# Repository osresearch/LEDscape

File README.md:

DANGER!
=======

This code works with the PRU units on the Beagle Bone and can easily
cause *hard crashes*.  It is still being debugged and developed.
Be careful hot-plugging things into the headers -- it is possible to
damage the pin drivers and cause problems in the ARM, especially if
there are +5V signals involved.

Overview
========

The WS281x LED chips are built like shift registers and make for very
easy LED strip construction.  The signals are duty-cycle modulated,
with a 0 measuring 250 ns long and a 1 being 600 ns long, and 1250 ns
between bits.  Since this doesn't map to normal SPI hardware and requires
an 800 KHz bit clock, it is typically handled with a dedicated microcontroller
or DMA hardware on something like the Teensy 3.

However, the TI AM335x ARM Cortex-A8 in the BeagleBone Black has two
programmable "microcontrollers" built into the CPU that can handle realtime
tasks and also access the ARM's memory.  This allows things that
might have been delegated to external devices to be handled without
any additional hardware, and without the overhead of clocking data out
the USB port.

The frames are stored in memory as a series of 4-byte pixels in the
order GRBA, packed in strip-major order.  This means that it looks
like this in RAM:

	S0P0 S1P0 S2P0 ... S31P0 S0P1 S1P1 ... S31P1 S0P2 S1P2 ... S31P2

This way length of the strip can be variable, although the memory used
will depend on the length of the longest strip.  4 * 32 * longest strip
bytes are required per frame buffer.  The maximum frame rate also depends
on the length of th elongest strip.

API
===

<ledscape.h> defines the API.  The sample rgb-test program pulses
the first three LEDs in red, green and blue.  The key components are:

	ledscape_t * ledscape_init(unsigned num_pixels)
	ledscape_frame_t * ledscape_frame(ledscape_t*, unsigned frame_num);
	ledscape_draw(ledscape_t*, unsigned frame_num);
	unsigned ledscape_wait(ledscape_t*)

You can double buffer like this:

	const int num_pixels = 256;
	ledscape_t * const leds = ledscape_init(num_pixels);

	unsigned i = 0;
	while (1)
	{
		// Alternate frame buffers on each draw command
		const unsigned frame_num = i++ % 2;
		ledscape_frame_t * const frame
			= ledscape_frame(leds, frame_num);

		render(frame);

		// wait for the previous frame to finish;
		ledscape_wait(leds);
		ledscape_draw(leds, frame_num);
	}

	ledscape_close(leds);

The 24-bit RGB data to be displayed is laid out with BRGA format,
since that is how it will be translated during the clock out from the PRU.
The frame buffer is stored as a "strip-major" array of pixels.

	typedef struct {
		uint8_t b;
		uint8_t r;
		uint8_t g;
		uint8_t a;
	} __attribute__((__packed__)) ledscape_pixel_t;

	typedef struct {
		ledscape_pixel_t strip[32];
	} __attribute__((__packed__)) ledscape_frame_t;

Low level API
=============

If you want to poke at the PRU directly, there is a command structure
shared in PRU DRAM that holds a pointer to the current frame buffer,
the length in pixels, a command byte and a response byte.
Once the PRU has cleared the command byte you are free to re-write the
dma address or number of pixels.

	typedef struct
	{
		// in the DDR shared with the PRU
		const uintptr_t pixels_dma;

		// Length in pixels of the longest LED strip.
		unsigned num_pixels;

		// write 1 to start, 0xFF to abort. will be cleared when started
		volatile unsigned command;

		// will have a non-zero response written when done
		volatile unsigned response;
	} __attribute__((__packed__)) ws281x_command_t;

LED Strips
==========

* http://www.adafruit.com/products/1138
* http://www.adafruit.com/datasheets/WS2811.pdf

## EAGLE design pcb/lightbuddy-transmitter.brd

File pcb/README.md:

Here are three PCB designs, for use with LEDscape:

octoscroller: Control 8 16x32 LED matricies directly from a BBB

LEDscape: Driver board for controlling 32 LED strips over RS485 connections
receiver: Receiver board which has 8x RS485 inputs, for control of up to 8 LED strips

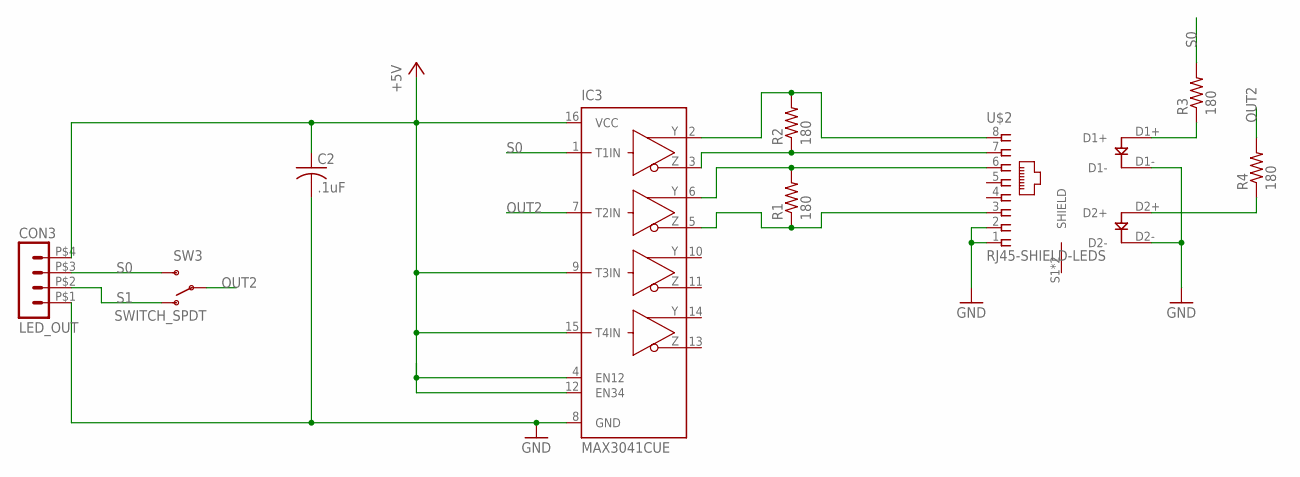
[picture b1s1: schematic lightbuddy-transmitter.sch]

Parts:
C2: .1uF; C0603
CON3: LED_OUT; DUPONT-4P
IC3: MAX3041CUE; TSSOP16
R1, R2, R3, R4: 180; R0603
SW3: SWITCH_SPDT; SWITCH_6P-2POS
U$2: RJ45-SHIELD-LEDS; RJ45-SHIELD-LEDS-ALT

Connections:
+5V: C2.1, CON3.P$4 (4), IC3.4 (EN12), IC3.9 (T3IN), IC3.12 (EN34), IC3.15 (T4IN), IC3.16 (VCC)
GND: C2.2, CON3.P$1 (1), IC3.8 (GND), U$2.1 (8), U$2.2 (7), U$2.D1-, U$2.D2-
unnamed: R3.1, U$2.D1+
unnamed: R4.1, U$2.D2+
unnamed: IC3.5 (Z2), R1.1, U$2.3 (6)
unnamed: IC3.2 (Y1), R2.2, U$2.8 (1)
unnamed: IC3.3 (Z1), R2.1, U$2.7 (2)
unnamed: IC3.6 (Y2), R1.2, U$2.6 (3)
OUT2: IC3.7 (T2IN), R4.2, SW3.P0, SW3.P1
S0: CON3.P$3 (3), IC3.1 (T1IN), R3.2, SW3.S0 (S), SW3.S1 (S)
S1: CON3.P$2 (2), SW3.O0 (O), SW3.O1 (O)

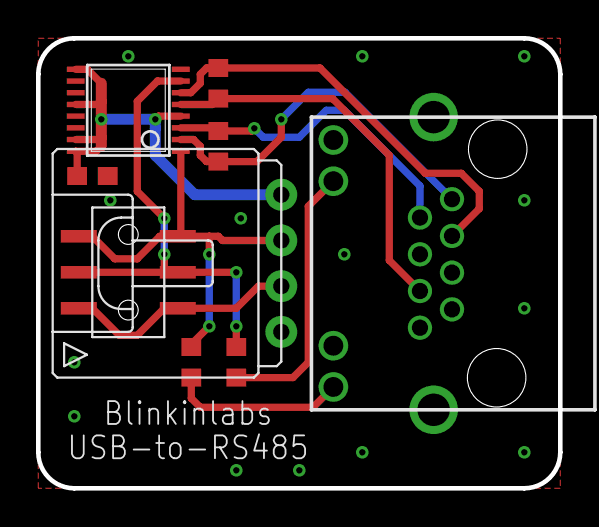
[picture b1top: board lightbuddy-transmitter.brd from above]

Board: 2 copper layers, 29.0 x 25.0 mm, 9 parts (0 on the bottom side), 11 nets.

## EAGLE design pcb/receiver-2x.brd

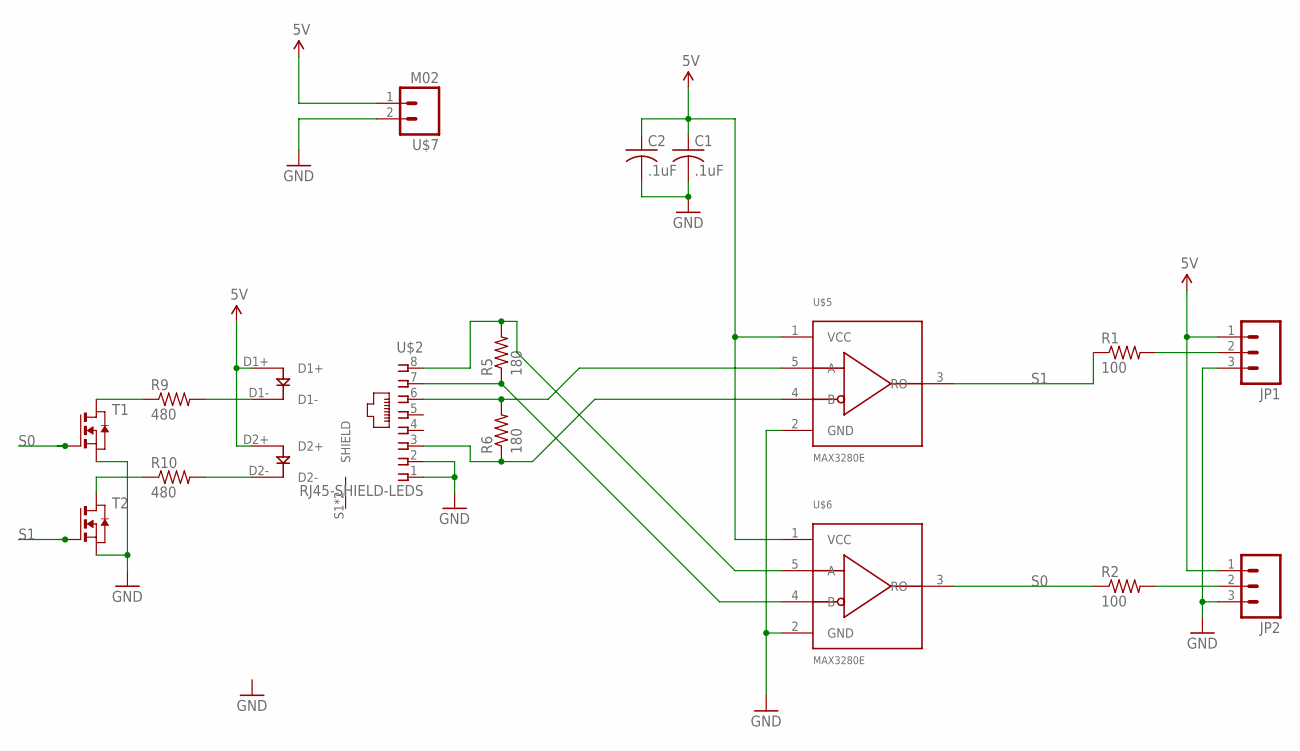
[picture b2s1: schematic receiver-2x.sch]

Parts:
C1, C2: .1uF; C0603
JP1, JP2: M03SCREW-DETACH; SCREWTERMINAL-5MM-3-DETACHABLE
R1, R2: 100; R0603
R5, R6: 180; R0603
R9, R10: 480; R0603
T1, T2: NMOSSOT23; SOT-23
U$2: RJ45-SHIELD-LEDS; RJ45-SHIELD-LEDS-ALT
U$5, U$6: MAX3280E; SOT23-5L
U$7: M02; SCREWTERMINAL-5MM-2-DETACHABLE

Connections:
5V: C1.1, C2.1, JP1.1, JP2.1, U$2.D1+, U$2.D2+, U$5.1 (VCC), U$6.1 (VCC), U$7.1
GND: C1.2, C2.2, JP1.3, JP2.3, T1.2 (S), T2.2 (S), U$2.1 (8), U$2.2 (7), U$5.2 (GND), U$6.2 (GND), U$7.2
unnamed: JP1.2, R1.2
unnamed: JP2.2, R2.2
unnamed: R10.2, U$2.D2-
unnamed: R9.2, U$2.D1-
unnamed: R10.1, T2.1 (D)
unnamed: R9.1, T1.1 (D)
S0: R2.1, T1.3 (G), U$6.3 (RO)
S0_IN+: R5.2, U$2.8 (1), U$6.5 (A)
S0_IN-: R5.1, U$2.7 (2), U$6.4 (B)
S1: R1.1, T2.3 (G), U$5.3 (RO)
S1_IN+: R6.2, U$2.6 (3), U$5.5 (A)
S1_IN-: R6.1, U$2.3 (6), U$5.4 (B)

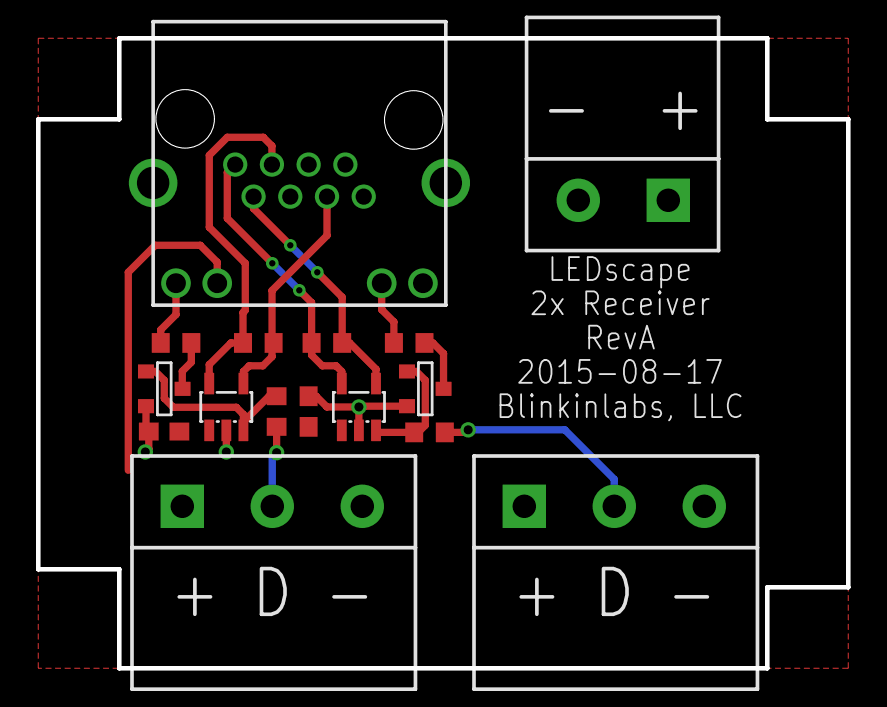
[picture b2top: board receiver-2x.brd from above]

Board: 2 copper layers, 45.0 x 35.0 mm, 17 parts (0 on the bottom side), 14 nets.

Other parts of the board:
U$3: DISORIENT_LOGO

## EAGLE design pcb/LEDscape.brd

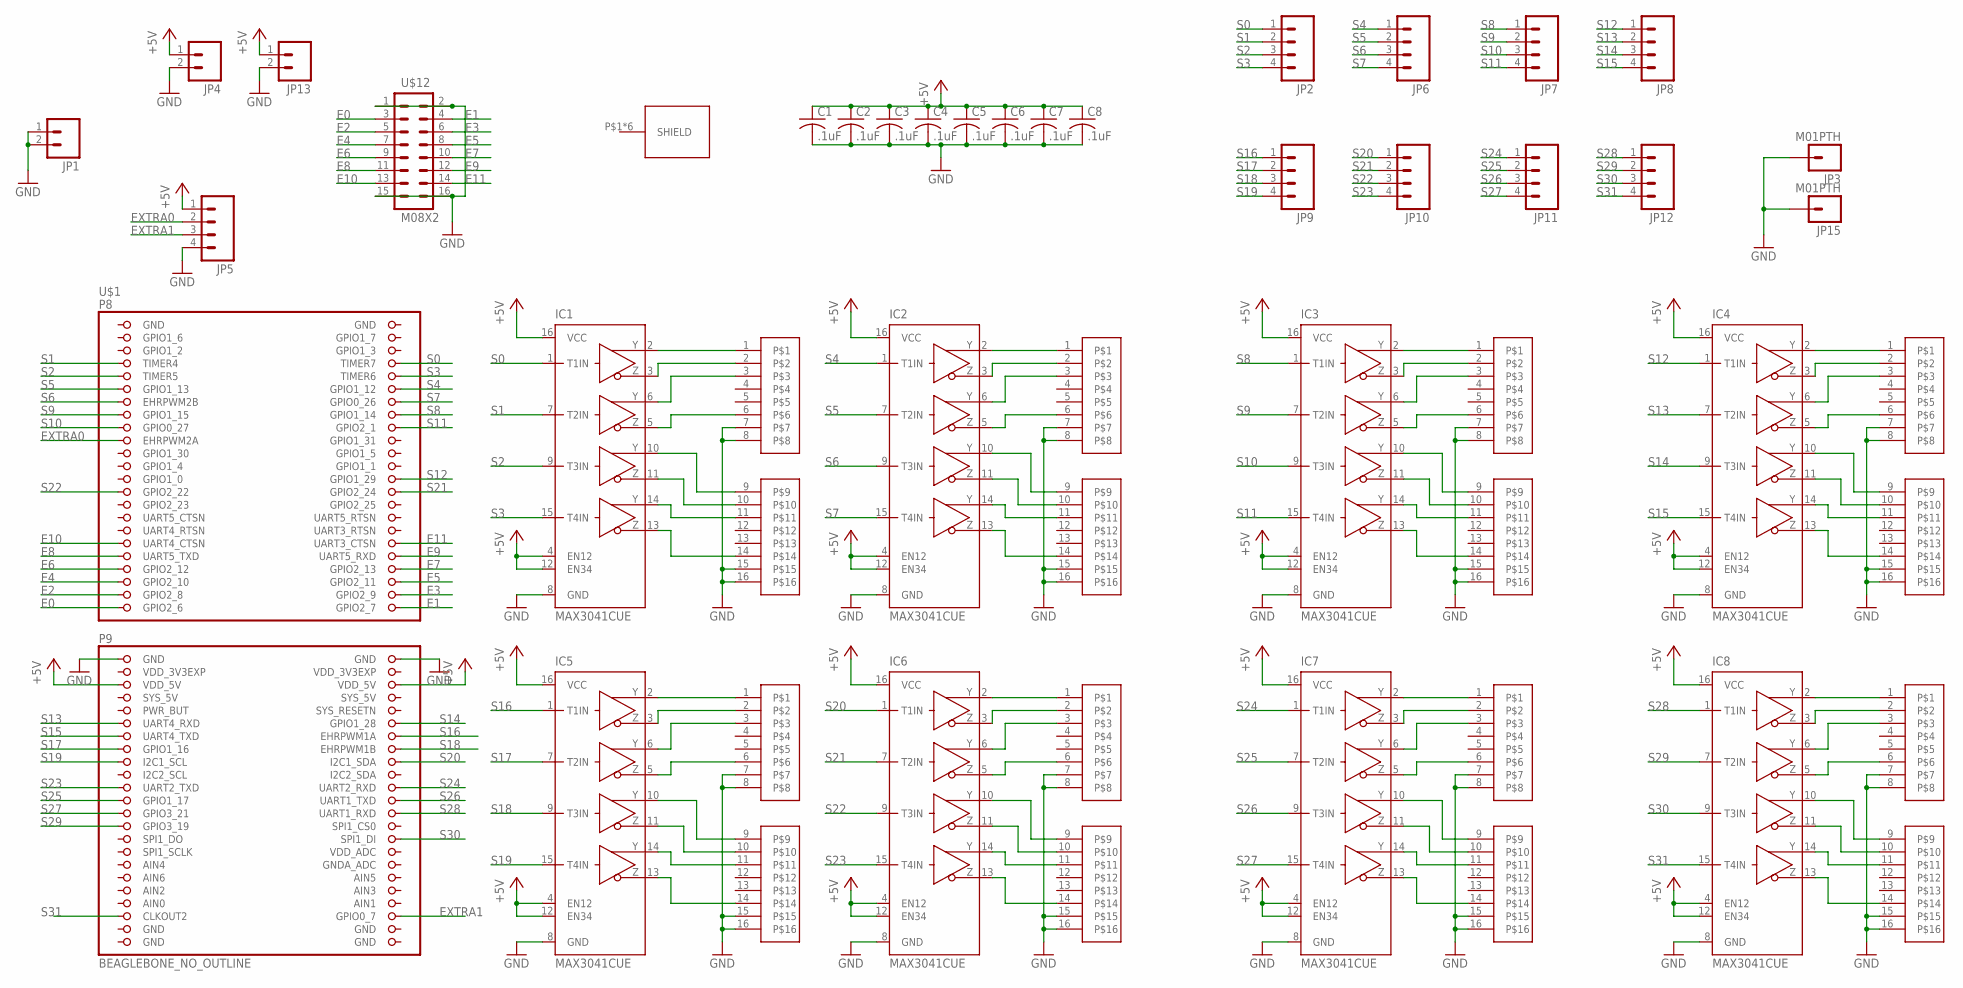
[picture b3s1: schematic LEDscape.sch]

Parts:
C1, C2, C3, C4, C5, C6, C7, C8: .1uF; C0603
IC1, IC2, IC3, IC4, IC5, IC6, IC7, IC8: MAX3041CUE; TSSOP16
JP1, JP4, JP13: M025MM; SCREWTERMINAL-5MM-2
JP2, JP5, JP6, JP7, JP8, JP9, JP10, JP11, JP12: M041X04_NO_SILK; 1X04_NO_SILK
JP3, JP15: M01PTH; 1X01
U$1: BEAGLEBONE_NO_OUTLINE; BEAGLEBONE_SHIELD_NO_OUTLINE
U$2: RJ45_8X2_BASE
U$3, U$4, U$5, U$6, U$7, U$8, U$9, U$10: RJ45_8X2_JACK
U$12: M08X2; 2X8

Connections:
+5V: C1.1, C2.1, C3.1, C4.1, C5.1, C6.1, C7.1, C8.1, IC1.4 (EN12), IC1.12 (EN34), IC1.16 (VCC), IC2.4 (EN12), IC2.12 (EN34), IC2.16 (VCC), IC3.4 (EN12), IC3.12 (EN34), IC3.16 (VCC), IC4.4 (EN12), IC4.12 (EN34), IC4.16 (VCC), IC5.4 (EN12), IC5.12 (EN34), IC5.16 (VCC), IC6.4 (EN12), IC6.12 (EN34), IC6.16 (VCC), IC7.4 (EN12), IC7.12 (EN34), IC7.16 (VCC), IC8.4 (EN12), IC8.12 (EN34), IC8.16 (VCC), JP4.1, JP5.1, JP13.1, U$1.51 (VDD_5V), U$1.52 (VDD_5V)
AIN0: U$1.85 (AIN0)
E0: U$1.45 (GPIO2_6), U$12.3
E1: U$1.46 (GPIO2_7), U$12.4
E2: U$1.43 (GPIO2_8), U$12.5
E3: U$1.44 (GPIO2_9), U$12.6
E4: U$1.41 (GPIO2_10), U$12.7
E5: U$1.42 (GPIO2_11), U$12.8
E6: U$1.39 (GPIO2_12), U$12.9
E7: U$1.40 (GPIO2_13), U$12.10
E8: U$1.37 (UART5_TXD), U$12.11
E9: U$1.38 (UART5_RXD), U$12.12
E10: U$1.35 (UART4_CTSN), U$12.13
E11: U$1.36 (UART3_CTSN), U$12.14
EXTRA0: JP5.2, U$1.19 (EHRPWM2A)
EXTRA1: JP5.3, U$1.88 (GPIO0_7)
GND: C1.2, C2.2, C3.2, C4.2, C5.2, C6.2, C7.2, C8.2, IC1.8 (GND), IC2.8 (GND), IC3.8 (GND), IC4.8 (GND), IC5.8 (GND), IC6.8 (GND), IC7.8 (GND), IC8.8 (GND), JP1.1, JP1.2, JP3.1, JP4.2, JP5.4, JP13.2, JP15.1, U$1.1 (GND), U$1.2 (GND), U$1.47 (GND), U$1.48 (GND), U$1.89 (GND), U$1.90 (GND), U$1.91 (GND), U$1.92 (GND), U$3.7, U$3.8, U$3.15, U$3.16, U$4.7, U$4.8, U$4.15, U$4.16, U$5.7, U$5.8, U$5.15, U$5.16, U$6.7, U$6.8, U$6.15, U$6.16, U$7.7, U$7.8, U$7.15, U$7.16, U$8.7, U$8.8, U$8.15, U$8.16, U$9.7, U$9.8, U$9.15, U$9.16, U$10.7, U$10.8, U$10.15, U$10.16, U$12.1, U$12.2, U$12.15, U$12.16
unnamed: IC1.2 (Y1), U$3.1
unnamed: IC1.3 (Z1), U$3.2
unnamed: IC2.2 (Y1), U$4.1
unnamed: IC1.6 (Y2), U$3.3
unnamed: IC1.5 (Z2), U$3.6
unnamed: IC1.10 (Y3), U$3.9
unnamed: IC1.11 (Z3), U$3.10
unnamed: IC1.14 (Y4), U$3.11
unnamed: IC1.13 (Z4), U$3.14
unnamed: IC2.3 (Z1), U$4.2
unnamed: IC6.5 (Z2), U$7.6
unnamed: IC2.6 (Y2), U$4.3
unnamed: IC2.5 (Z2), U$4.6
unnamed: IC3.5 (Z2), U$5.6
unnamed: IC2.10 (Y3), U$4.9
unnamed: IC2.11 (Z3), U$4.10
unnamed: IC2.14 (Y4), U$4.11
unnamed: IC2.13 (Z4), U$4.14
unnamed: IC3.2 (Y1), U$5.1
unnamed: IC3.3 (Z1), U$5.2
unnamed: IC3.6 (Y2), U$5.3
unnamed: IC3.13 (Z4), U$5.14
unnamed: IC3.10 (Y3), U$5.9
unnamed: IC3.11 (Z3), U$5.10
unnamed: IC3.14 (Y4), U$5.11
unnamed: IC7.6 (Y2), U$8.3
unnamed: IC4.2 (Y1), U$9.1
unnamed: IC4.3 (Z1), U$9.2
unnamed: IC4.6 (Y2), U$9.3
unnamed: IC4.5 (Z2), U$9.6
unnamed: IC4.13 (Z4), U$9.14
unnamed: IC4.11 (Z3), U$9.10
unnamed: IC4.14 (Y4), U$9.11
unnamed: IC4.10 (Y3), U$9.9
unnamed: IC5.2 (Y1), U$6.1
unnamed: IC5.3 (Z1), U$6.2
unnamed: IC5.6 (Y2), U$6.3
unnamed: IC5.5 (Z2), U$6.6
unnamed: IC5.10 (Y3), U$6.9
unnamed: IC5.11 (Z3), U$6.10
unnamed: IC5.14 (Y4), U$6.11
unnamed: IC5.13 (Z4), U$6.14
unnamed: IC6.2 (Y1), U$7.1
unnamed: IC6.3 (Z1), U$7.2
unnamed: IC6.6 (Y2), U$7.3
unnamed: IC7.5 (Z2), U$8.6
unnamed: IC6.10 (Y3), U$7.9
unnamed: IC6.11 (Z3), U$7.10
unnamed: IC6.14 (Y4), U$7.11
unnamed: IC6.13 (Z4), U$7.14
unnamed: IC7.2 (Y1), U$8.1
unnamed: IC7.3 (Z1), U$8.2
unnamed: IC7.10 (Y3), U$8.9
unnamed: IC7.14 (Y4), U$8.11
unnamed: IC7.13 (Z4), U$8.14
unnamed: IC7.11 (Z3), U$8.10
unnamed: IC8.6 (Y2), U$10.3
unnamed: IC8.2 (Y1), U$10.1
unnamed: IC8.3 (Z1), U$10.2
unnamed: IC8.5 (Z2), U$10.6
unnamed: IC8.14 (Y4), U$10.11
unnamed: IC8.10 (Y3), U$10.9
unnamed: IC8.11 (Z3), U$10.10
unnamed: IC8.13 (Z4), U$10.14
S0: IC1.1 (T1IN), JP2.1, U$1.8 (TIMER7)
S1: IC1.7 (T2IN), JP2.2, U$1.7 (TIMER4)
S2: IC1.9 (T3IN), JP2.3, U$1.9 (TIMER5)
S3: IC1.15 (T4IN), JP2.4, U$1.10 (TIMER6)
S4: IC2.1 (T1IN), JP6.1, U$1.12 (GPIO1_12)
S5: IC2.7 (T2IN), JP6.2, U$1.11 (GPIO1_13)
S6: IC2.9 (T3IN), JP6.3, U$1.13 (EHRPWM2B)
S7: IC2.15 (T4IN), JP6.4, U$1.14 (GPIO0_26)
S8: IC3.1 (T1IN), JP7.1, U$1.16 (GPIO1_14)
S9: IC3.7 (T2IN), JP7.2, U$1.15 (GPIO1_15)
S10: IC3.9 (T3IN), JP7.3, U$1.17 (GPIO0_27)
S11: IC3.15 (T4IN), JP7.4, U$1.18 (GPIO2_1)
S12: IC4.1 (T1IN), JP8.1, U$1.26 (GPIO1_29)
S13: IC4.7 (T2IN), JP8.2, U$1.57 (UART4_RXD)
S14: IC4.9 (T3IN), JP8.3, U$1.58 (GPIO1_28)
S15: IC4.15 (T4IN), JP8.4, U$1.59 (UART4_TXD)
S16: IC5.1 (T1IN), JP9.1, U$1.60 (EHRPWM1A)
S17: IC5.7 (T2IN), JP9.2, U$1.61 (GPIO1_16)
S18: IC5.9 (T3IN), JP9.3, U$1.62 (EHRPWM1B)
S19: IC5.15 (T4IN), JP9.4, U$1.63 (I2C1_SCL)
S20: IC6.1 (T1IN), JP10.1, U$1.64 (I2C1_SDA)
S21: IC6.7 (T2IN), JP10.2, U$1.28 (GPIO2_24)
S22: IC6.9 (T3IN), JP10.3, U$1.27 (GPIO2_22)
S23: IC6.15 (T4IN), JP10.4, U$1.67 (UART2_TXD)
S24: IC7.1 (T1IN), JP11.1, U$1.68 (UART2_RXD)
S25: IC7.7 (T2IN), JP11.2, U$1.69 (GPIO1_17)
S26: IC7.9 (T3IN), JP11.3, U$1.70 (UART1_TXD)
S27: IC7.15 (T4IN), JP11.4, U$1.71 (GPIO3_21)
S28: IC8.1 (T1IN), JP12.1, U$1.72 (UART1_RXD)
S29: IC8.7 (T2IN), JP12.2, U$1.73 (GPIO3_19)
S30: IC8.9 (T3IN), JP12.3, U$1.76 (SPI1_DI)
S31: IC8.15 (T4IN), JP12.4, U$1.87 (CLKOUT2)
SYS_5V: U$1.53 (SYS_5V)
VDD_3V3EXP: U$1.49 (VDD_3V3EXP), U$1.50 (VDD_3V3EXP)

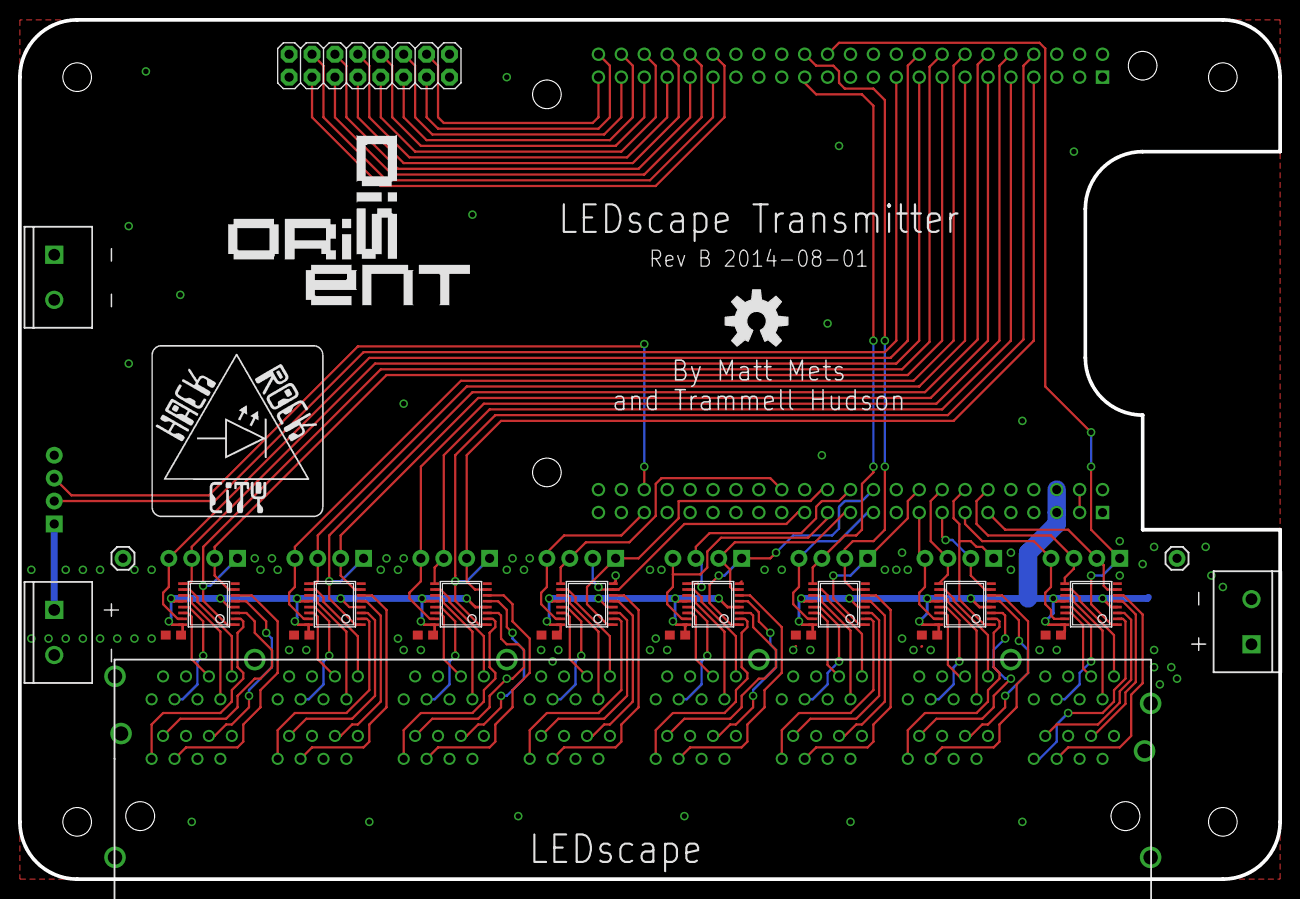
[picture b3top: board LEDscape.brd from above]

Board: 2 copper layers, 139.7 x 95.2 mm, 44 parts (1 on the bottom side), 113 nets.

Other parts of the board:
U$11: OSHW-LOGO-L
U$13: HRC_LOGO_0.75IN
U$14: DISORIENT_LOGO

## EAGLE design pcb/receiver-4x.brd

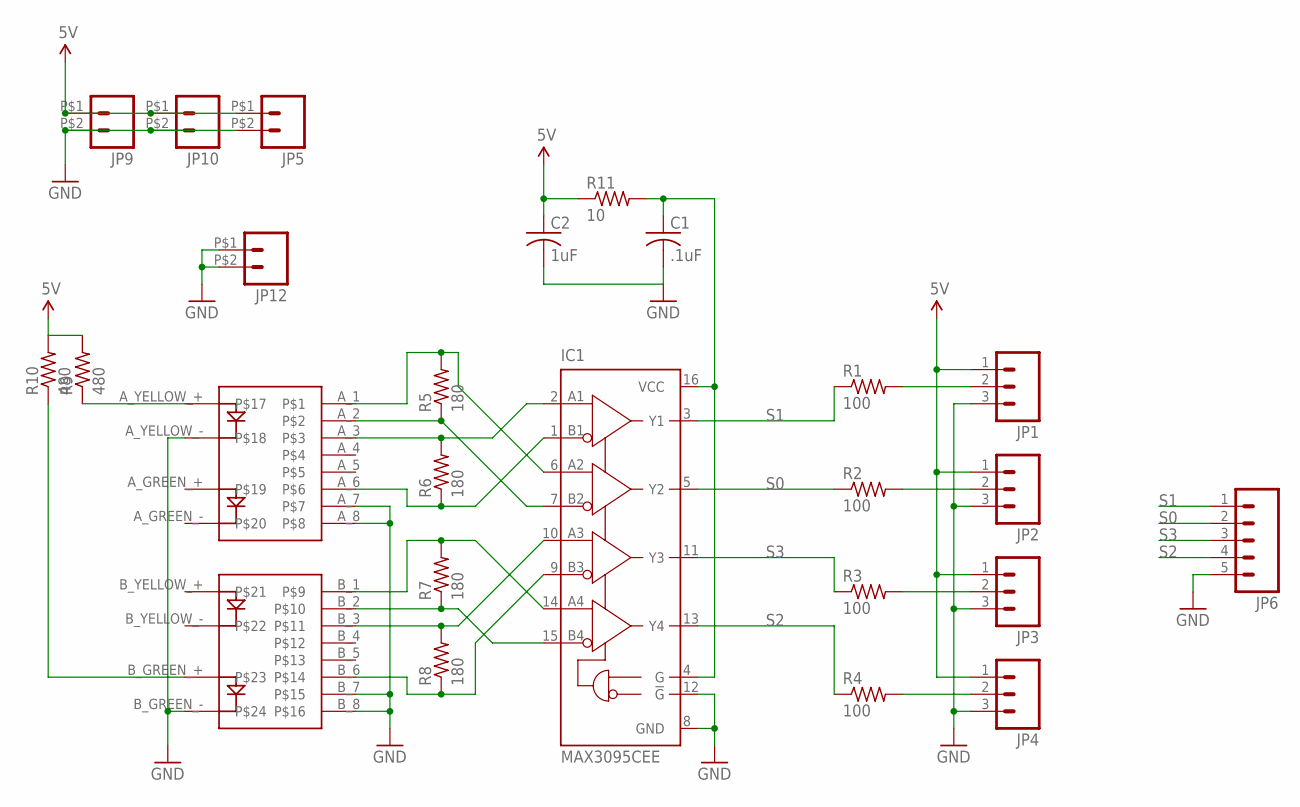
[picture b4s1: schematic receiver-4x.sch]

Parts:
C1: .1uF; C0603
C2: 1uF; C0603
IC1: MAX3095CEE; QSOP16
JP1, JP2, JP3, JP4: M03SCREW-DETACH; SCREWTERMINAL-5MM-3-DETACHABLE
JP5, JP9, JP10, JP12: M026.35MM; SCREWTERMINAL-6.35MM-2
JP6: M05PTH; 1X05
R1, R2, R3, R4: 100; R0603
R5, R6, R7, R8: 180; R0603
R9, R10: 480; R0603
R11: 10; R0603
U$1: RJ45_2X1

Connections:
5V: C2.1, JP1.1, JP2.1, JP3.1, JP4.1, JP5.P$1 (1), JP9.P$1 (1), JP10.P$1 (1), R9.2, R10.2, R11.1
GND: C1.2, C2.2, IC1.8 (GND), IC1.12 (!G), JP1.3, JP2.3, JP3.3, JP4.3, JP5.P$2 (2), JP6.5, JP9.P$2 (2), JP10.P$2 (2), JP12.P$1 (1), JP12.P$2 (2), U$1.A_7, U$1.A_8, U$1.A_YELLOW_-, U$1.B_7, U$1.B_8, U$1.B_GREEN_-
unnamed: JP1.2, R1.2
unnamed: IC1.6 (A2), R5.2, U$1.A_1
unnamed: IC1.7 (B2), R5.1, U$1.A_2
unnamed: JP2.2, R2.2
unnamed: JP3.2, R3.2
unnamed: JP4.2, R4.2
unnamed: IC1.2 (A1), R6.2, U$1.A_3
unnamed: IC1.1 (B1), R6.1, U$1.A_6
unnamed: IC1.14 (A4), R7.2, U$1.B_1
unnamed: IC1.15 (B4), R7.1, U$1.B_2
unnamed: IC1.10 (A3), R8.2, U$1.B_3
unnamed: IC1.9 (B3), R8.1, U$1.B_6
unnamed: R9.1, U$1.A_YELLOW_+
unnamed: R10.1, U$1.B_GREEN_+
unnamed: C1.1, IC1.4 (G), IC1.16 (VCC), R11.2
S0: IC1.5 (Y2), JP6.2, R2.1
S1: IC1.3 (Y1), JP6.1, R1.1
S2: IC1.13 (Y4), JP6.4, R4.1
S3: IC1.11 (Y3), JP6.3, R3.1

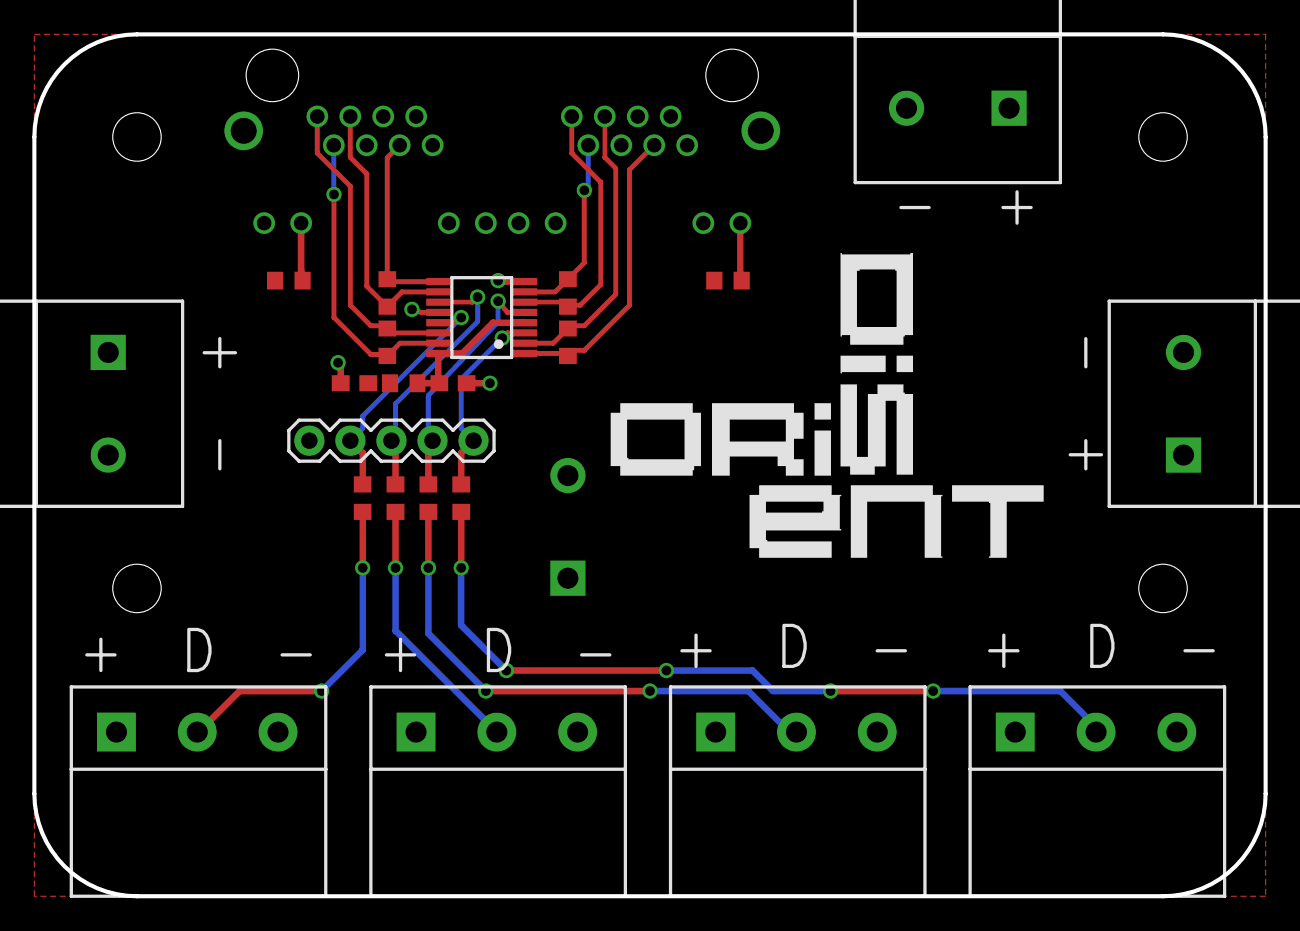
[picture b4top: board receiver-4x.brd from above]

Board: 2 copper layers, 76.2 x 53.3 mm, 25 parts (1 on the bottom side), 21 nets.

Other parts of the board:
U$3: DISORIENT_LOGO

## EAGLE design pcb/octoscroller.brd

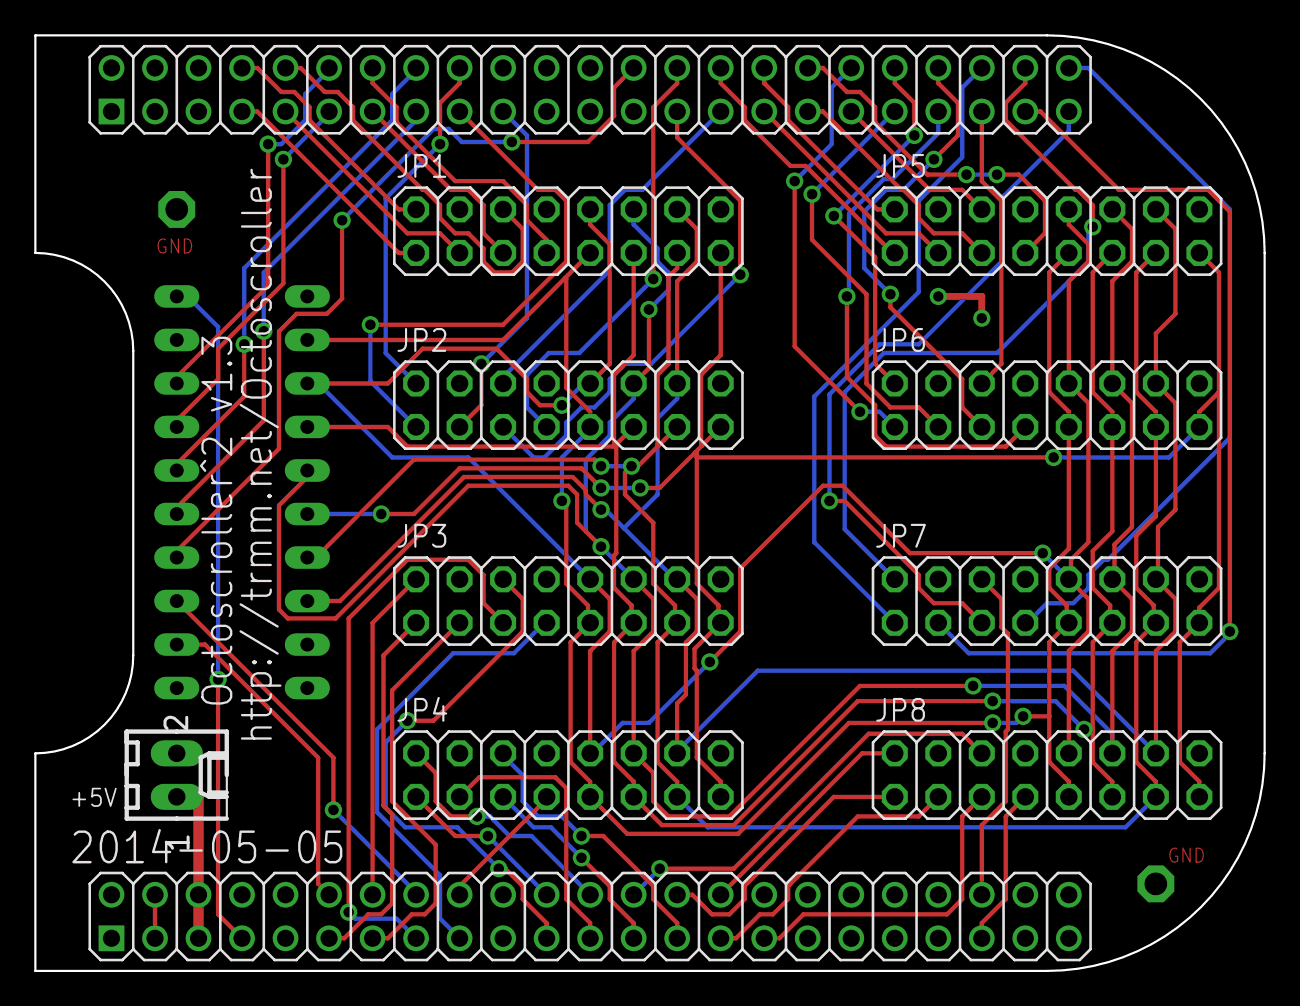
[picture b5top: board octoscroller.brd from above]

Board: 2 copper layers, 71.8 x 54.6 mm, 13 parts (1 on the bottom side), 66 nets.

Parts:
+5V: 22-27-2021-02; 6410-02
IC1: 74LS245N; DIL20
JP1, JP2, JP3, JP4, JP5, JP6, JP7, JP8: 2X08
TP1, TP2: PTR1PAD1-13; P1-13
U$1: BEAGLEBONE_OUTLINE; BEAGLEBONE_SHIELD

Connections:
+5V: IC1.20, U$1.53
+5V-IN: +5V.1, U$1.51, U$1.52
A: IC1.2, JP1.9, JP2.9, JP3.9, JP4.9, JP5.9, JP6.9, JP7.9, JP8.9
A_RAW: IC1.18, U$1.12
B: IC1.3, JP1.10, JP2.10, JP3.10, JP4.10, JP5.10, JP6.10, JP7.10, JP8.10
B1.1: JP1.3, U$1.9
B1.2: JP1.7, U$1.14
B2.1: JP2.3, U$1.19
B2.2: JP2.7, U$1.28
B3.1: JP3.3, U$1.59
B3.2: JP3.7, U$1.63
B4.1: JP4.3, U$1.69
B4.2: JP4.7, U$1.64
B5.1: JP5.3, U$1.31
B5.2: JP5.7, U$1.34
B6.1: JP6.3, U$1.37
B6.2: JP6.7, U$1.39
B7.1: JP7.3, U$1.43
B7.2: JP7.7, U$1.46
B8.1: JP8.3, U$1.75
B8.2: JP8.7, U$1.87
B_RAW: IC1.17, U$1.11
C: IC1.4, JP1.11, JP2.11, JP3.11, JP4.11, JP5.11, JP6.11, JP7.11, JP8.11
CLK: IC1.7, JP1.13, JP2.13, JP3.13, JP4.13, JP5.13, JP6.13, JP7.13, JP8.13
CLK_RAW: IC1.13, U$1.62
C_RAW: IC1.16, U$1.16
D: IC1.5, JP1.12, JP2.12, JP3.12, JP4.12, JP5.12, JP6.12, JP7.12, JP8.12
D_RAW: IC1.15, U$1.15
G1.1: JP1.2, U$1.8
G1.2: JP1.6, U$1.10
G2.1: JP2.2, U$1.18
G2.2: JP2.6, U$1.29
G3.1: JP3.2, U$1.60
G3.2: JP3.6, U$1.67
G4.1: JP4.2, U$1.70
G4.2: JP4.6, U$1.73
G5.1: JP5.2, U$1.32
G5.2: JP5.6, U$1.35
G6.1: JP6.2, U$1.38
G6.2: JP6.6, U$1.41
G7.1: JP7.2, U$1.44
G7.2: JP7.6, U$1.88
G8.1: JP8.2, U$1.76
G8.2: JP8.6, U$1.72
GND: +5V.2, IC1.1, IC1.10, IC1.19, JP1.4, JP1.8, JP1.16, JP2.4, JP2.8, JP2.16, JP3.4, JP3.8, JP3.16, JP4.4, JP4.8, JP4.16, JP5.4, JP5.8, JP5.16, JP6.4, JP6.8, JP6.16, JP7.4, JP7.8, JP7.16, JP8.4, JP8.8, JP8.16, TP1.TP, TP2.TP, U$1.1, U$1.2, U$1.47, U$1.48, U$1.89, U$1.90, U$1.91, U$1.92
LATCH: IC1.8, JP1.14, JP2.14, JP3.14, JP4.14, JP5.14, JP6.14, JP7.14, JP8.14
LATCH_RAW: IC1.12, U$1.58
OE: IC1.6, JP1.15, JP2.15, JP3.15, JP4.15, JP5.15, JP6.15, JP7.15, JP8.15
OE_RAW: IC1.14, U$1.26
R1.1: JP1.1, U$1.7
R1.2: JP1.5, U$1.13
R2.1: JP2.1, U$1.17
R2.2: JP2.5, U$1.27
R3.1: JP3.1, U$1.57
R3.2: JP3.5, U$1.61
R4.1: JP4.1, U$1.68
R4.2: JP4.5, U$1.71
R5.1: JP5.1, U$1.30
R5.2: JP5.5, U$1.33
R6.1: JP6.1, U$1.36
R6.2: JP6.5, U$1.40
R7.1: JP7.1, U$1.42
R7.2: JP7.5, U$1.45
R8.1: JP8.1, U$1.74
R8.2: JP8.5, U$1.77
VDD_3V3EXP: U$1.49, U$1.50

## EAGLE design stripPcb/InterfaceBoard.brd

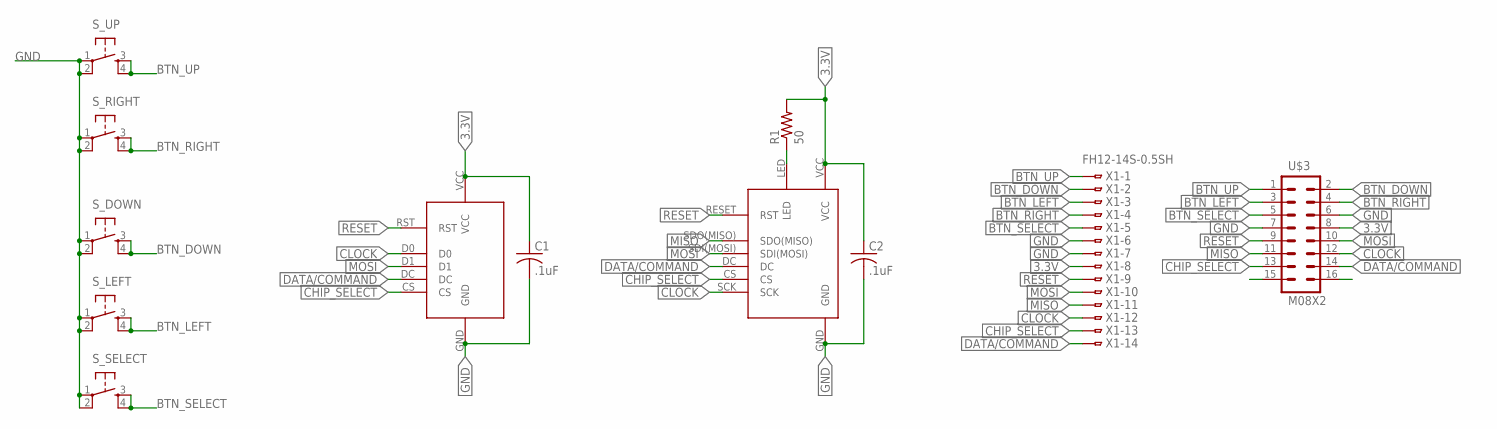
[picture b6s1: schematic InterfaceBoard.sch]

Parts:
C1, C2: .1uF; C0603
R1: 50; R0603
S_DOWN: TAC_SWITCHSMD; TACTILE_SWITCH_SMD
S_LEFT: TAC_SWITCHSMD; TACTILE_SWITCH_SMD
S_RIGHT: TAC_SWITCHSMD; TACTILE_SWITCH_SMD
S_SELECT: TAC_SWITCHSMD; TACTILE_SWITCH_SMD
S_UP: TAC_SWITCHSMD; TACTILE_SWITCH_SMD
U$1: OLED_XYDZ_13
U$2: LCD_QDTECH_22
U$3: M08X2; 2X8
X1: FH12-14S-0.5SH

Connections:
3.3V: C1.1, C2.1, R1.2, U$1.VCC, U$2.VCC, U$3.8, X1.8
BTN_DOWN: S_DOWN.3, S_DOWN.4, U$3.2, X1.2
BTN_LEFT: S_LEFT.3, S_LEFT.4, U$3.3, X1.3
BTN_RIGHT: S_RIGHT.3, S_RIGHT.4, U$3.4, X1.4
BTN_SELECT: S_SELECT.3, S_SELECT.4, U$3.5, X1.5
BTN_UP: S_UP.3, S_UP.4, U$3.1, X1.1
CHIP_SELECT: U$1.CS, U$2.CS, U$3.13, X1.13
CLOCK: U$1.D0, U$2.SCK, U$3.12, X1.12
DATA/COMMAND: U$1.DC, U$2.DC, U$3.14, X1.14
GND: C1.2, C2.2, S_DOWN.1, S_DOWN.2, S_LEFT.1, S_LEFT.2, S_RIGHT.1, S_RIGHT.2, S_SELECT.1, S_SELECT.2, S_UP.1, S_UP.2, U$1.GND, U$2.GND, U$3.6, U$3.7, X1.6, X1.7
MISO: U$2.SDO(MISO), U$3.11, X1.11
MOSI: U$1.D1, U$2.SDI(MOSI), U$3.10, X1.10
unnamed: R1.1, U$2.LED
RESET: U$1.RST, U$2.RESET (RST), U$3.9, X1.9

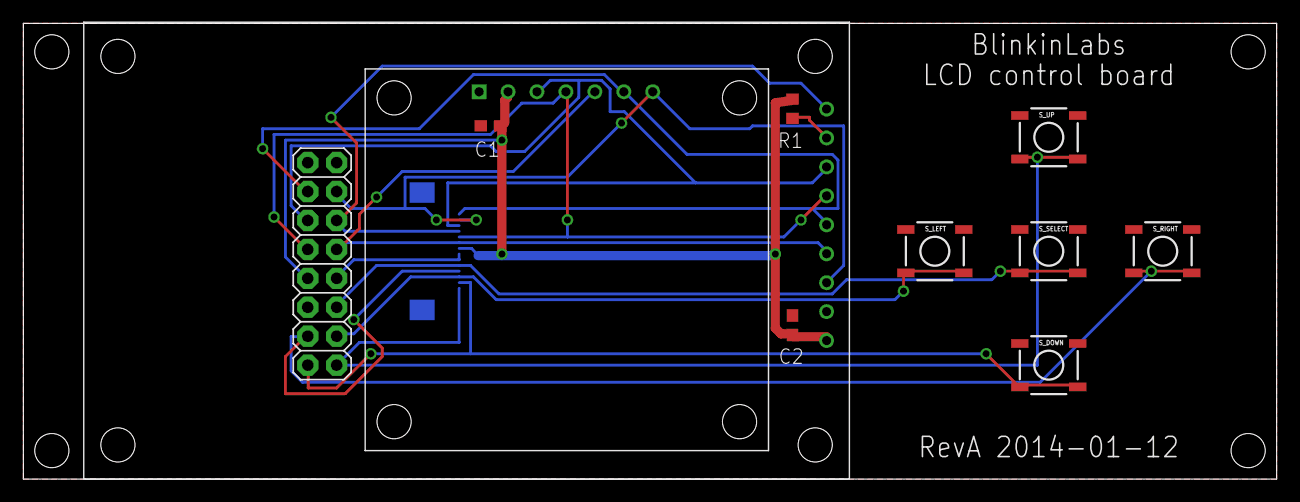
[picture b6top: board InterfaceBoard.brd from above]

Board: 2 copper layers, 110.0 x 40.0 mm, 12 parts (1 on the bottom side), 14 nets.

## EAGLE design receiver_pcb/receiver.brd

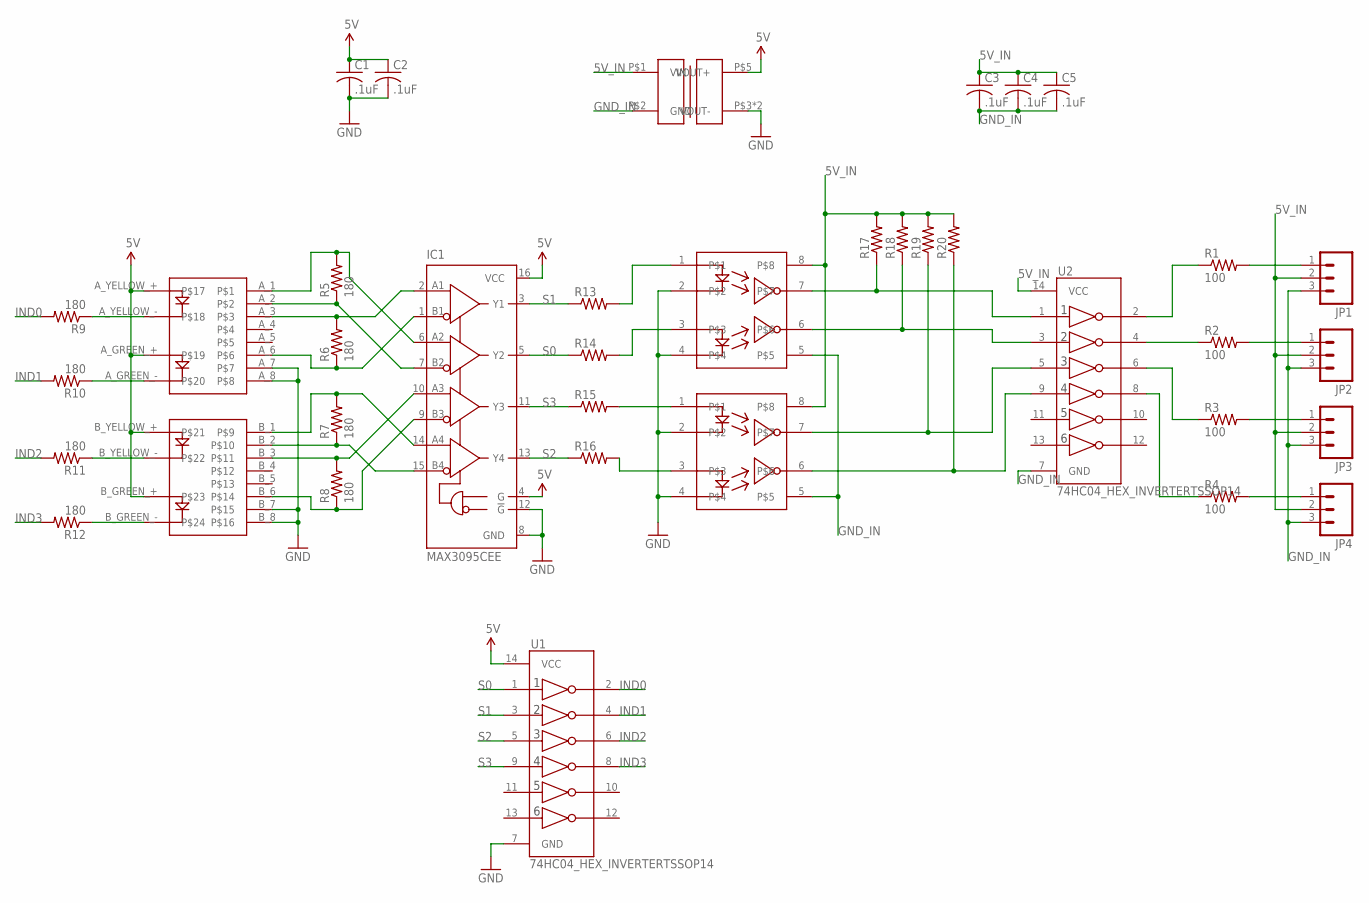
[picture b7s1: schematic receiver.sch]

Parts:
C1, C2, C3, C4, C5: .1uF; C0603
IC1: MAX3095CEE; QSOP16
JP1, JP2, JP3, JP4: M03-SCREW-5MM; SCREWTERMINAL-5MM-3
R1, R2, R3, R4: 100; R0603
R5, R6, R7, R8, R9, R10, R11, R12: 180; R0603
R13, R14, R15, R16, R17, R18, R19, R20: R-US_R0603; R0603
U1, U2: 74HC04_HEX_INVERTERTSSOP14; TSSOP14
U$1: RJ45_2X1
U$2: DC_DC_ISOLATED_0505; IB_XLS-1W
U$3, U$4: HCPL-0631-500E; SO08

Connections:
5V: C1.1, C2.1, IC1.4 (G), IC1.16 (VCC), U1.14 (VCC), U$1.A_GREEN_+, U$1.A_YELLOW_+, U$1.B_GREEN_+, U$1.B_YELLOW_+, U$2.P$5 (VOUT+)
5V_IN: C3.1, C4.1, C5.1, JP1.2, JP2.2, JP3.2, JP4.2, R17.2, R18.2, R19.2, R20.2, U2.14 (VCC), U$2.P$1 (VIN), U$3.8, U$4.8
GND: C1.2, C2.2, IC1.8 (GND), IC1.12 (!G), U1.7 (GND), U$1.A_7, U$1.A_8, U$1.B_7, U$1.B_8, U$2.P$3 (VOUT-), U$2.P$4 (VOUT-), U$3.2, U$3.4, U$4.2, U$4.4
GND_IN: C3.2, C4.2, C5.2, JP1.3, JP2.3, JP3.3, JP4.3, U2.7 (GND), U$2.P$2 (GND), U$3.5, U$4.5
IND0: R9.2, U1.2 (1Y)
IND1: R10.2, U1.4 (2Y)
IND2: R11.2, U1.6 (3Y)
IND3: R12.2, U1.8 (4Y)
unnamed: JP1.1, R1.2
unnamed: IC1.6 (A2), R5.2, U$1.A_1
unnamed: IC1.7 (B2), R5.1, U$1.A_2
unnamed: JP2.1, R2.2
unnamed: JP3.1, R3.2
unnamed: JP4.1, R4.2
unnamed: R9.1, U$1.A_YELLOW_-
unnamed: IC1.2 (A1), R6.2, U$1.A_3
unnamed: IC1.1 (B1), R6.1, U$1.A_6
unnamed: IC1.14 (A4), R7.2, U$1.B_1
unnamed: IC1.15 (B4), R7.1, U$1.B_2
unnamed: IC1.10 (A3), R8.2, U$1.B_3
unnamed: IC1.9 (B3), R8.1, U$1.B_6
unnamed: R10.1, U$1.A_GREEN_-
unnamed: R11.1, U$1.B_YELLOW_-
unnamed: R12.1, U$1.B_GREEN_-
unnamed: R13.2, U$3.1
unnamed: R14.2, U$3.3
unnamed: R15.2, U$4.1
unnamed: R16.2, U$4.3
unnamed: R18.1, U2.3 (2A), U$3.6
unnamed: R17.1, U2.1 (1A), U$3.7
unnamed: R19.1, U2.5 (3A), U$4.7
unnamed: R20.1, U2.9 (4A), U$4.6
unnamed: R1.1, U2.2 (1Y)
unnamed: R2.1, U2.4 (2Y)
unnamed: R3.1, U2.6 (3Y)
unnamed: R4.1, U2.8 (4Y)
S0: IC1.5 (Y2), R14.1, U1.1 (1A)
S1: IC1.3 (Y1), R13.1, U1.3 (2A)
S2: IC1.13 (Y4), R16.1, U1.5 (3A)
S3: IC1.11 (Y3), R15.1, U1.9 (4A)

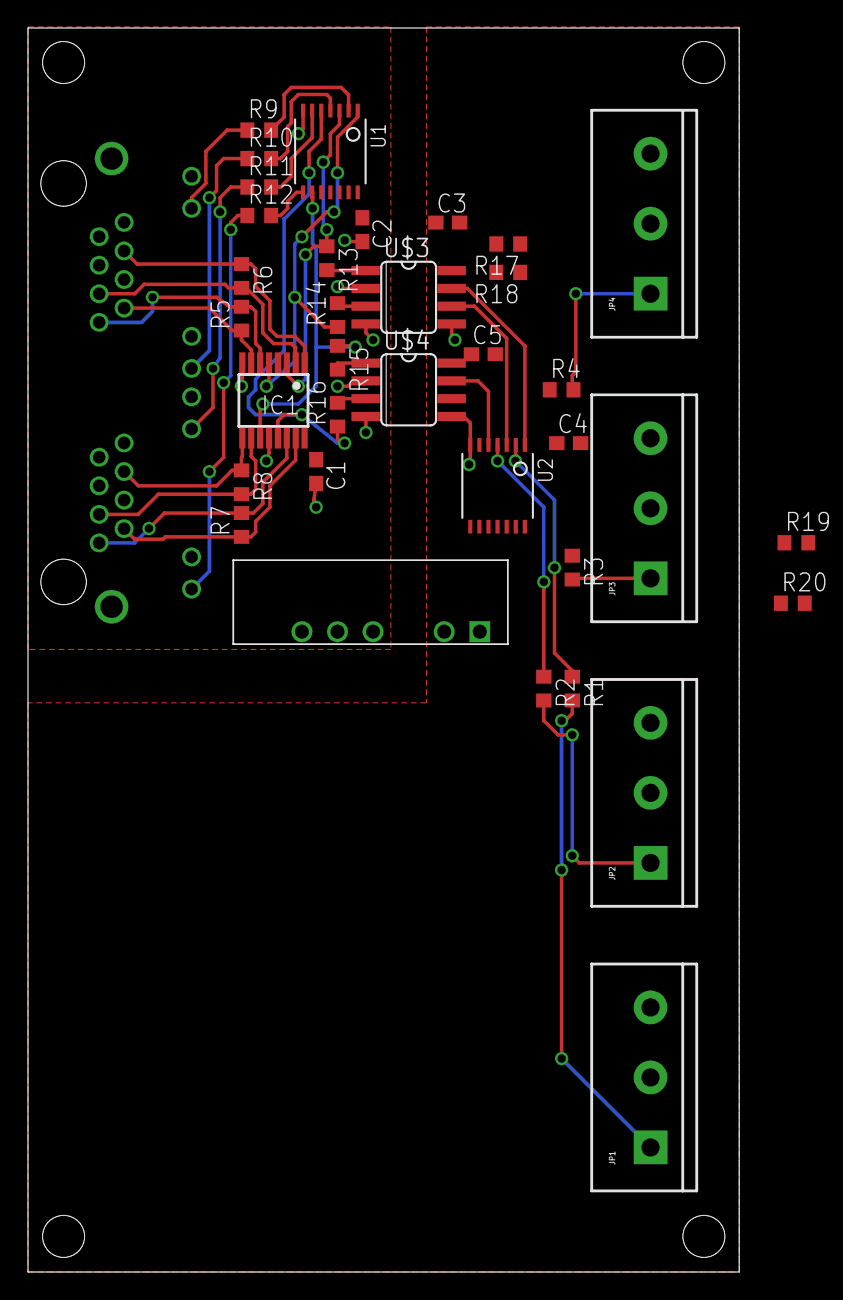
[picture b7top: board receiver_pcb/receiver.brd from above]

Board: 2 copper layers, 50.8 x 88.8 mm, 36 parts (0 on the bottom side), 40 nets.

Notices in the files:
parts and their libraries:
SparkFun-Connectors: Licensing: CC v3.0 Share-Alike You are welcome to use this library for commercial purposes.
